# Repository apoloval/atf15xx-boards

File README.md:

# ATF15xx Boards

This repository contains PCB designs for programming and prototyping boards for Atmel ATF15xx CPLDs family.

## Contents

- [atf15xxprog-plcc44](./atf15xxprog-plcc44): A broadboard adapter with JTAG connector to program ATF1502 and ATF1504 CPLDs with PLCC44 packaging.

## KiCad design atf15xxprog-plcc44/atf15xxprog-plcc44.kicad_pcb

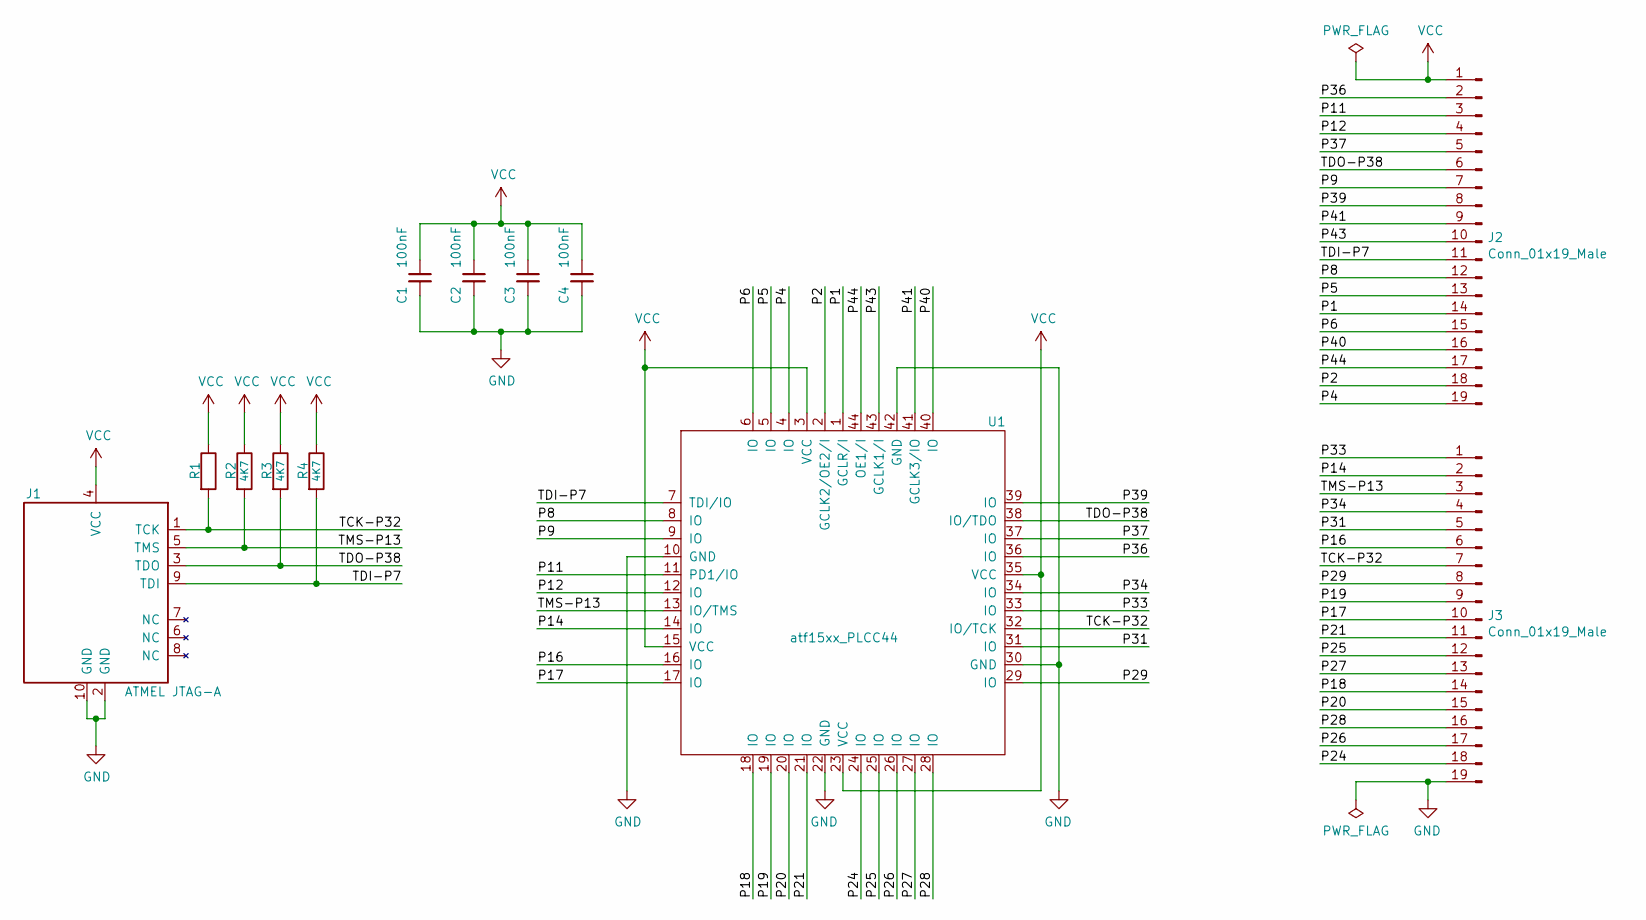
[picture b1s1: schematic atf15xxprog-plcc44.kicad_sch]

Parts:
C1, C2, C3, C4: 100nF; C_1206_3216Metric
J1: ATMEL JTAG-A; IDC-Header_2x05_P2.54mm_Vertical
J2, J3: Conn_01x19_Male; PinHeader_1x19_P2.54mm_Vertical
R1: (no value)
R2, R3, R4: 4K7
U1: atf15xx_PLCC44; PLCC-44_THT-Socket

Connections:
/P1: J2.14, U1.1 (GCLR/I)
/P2: J2.18, U1.2 (GCLK2/OE2/I)
/P4: J2.19, U1.4 (IO)
/P5: J2.13, U1.5 (IO)
/P6: J2.15, U1.6 (IO)
/P8: J2.12, U1.8 (IO)
/P9: J2.7, U1.9 (IO)
/P11: J2.3, U1.11 (PD1/IO)
/P12: J2.4, U1.12 (IO)
/P14: J3.2, U1.14 (IO)
/P16: J3.6, U1.16 (IO)
/P17: J3.10, U1.17 (IO)
/P18: J3.14, U1.18 (IO)
/P19: J3.9, U1.19 (IO)
/P20: J3.15, U1.20 (IO)
/P21: J3.11, U1.21 (IO)
/P24: J3.18, U1.24 (IO)
/P25: J3.12, U1.25 (IO)
/P26: J3.17, U1.26 (IO)
/P27: J3.13, U1.27 (IO)
/P28: J3.16, U1.28 (IO)
/P29: J3.8, U1.29 (IO)
/P31: J3.5, U1.31 (IO)
/P33: J3.1, U1.33 (IO)
/P34: J3.4, U1.34 (IO)
/P36: J2.2, U1.36 (IO)
/P37: J2.5, U1.37 (IO)
/P39: J2.8, U1.39 (IO)
/P40: J2.16, U1.40 (IO)
/P41: J2.9, U1.41 (GCLK3/IO)
/P43: J2.10, U1.43 (GCLK1/I)
/P44: J2.17, U1.44 (OE1/I)
/TCK-P32: J1.1 (TCK), J3.7, R1.2, U1.32 (IO/TCK)
/TDI-P7: J1.9 (TDI), J2.11, R4.2, U1.7 (TDI/IO)
/TDO-P38: J1.3 (TDO), J2.6, R3.2, U1.38 (IO/TDO)
/TMS-P13: J1.5 (TMS), J3.3, R2.2, U1.13 (IO/TMS)
GND: C1.2, C2.2, C3.2, C4.2, J1.2 (GND), J1.10 (GND), J3.19, U1.10 (GND), U1.22 (GND), U1.30 (GND), U1.42 (GND)
VCC: C1.1, C2.1, C3.1, C4.1, J1.4 (VCC), J2.1, R1.1, R2.1, R3.1, R4.1, U1.3 (VCC), U1.15 (VCC), U1.23 (VCC), U1.35 (VCC)

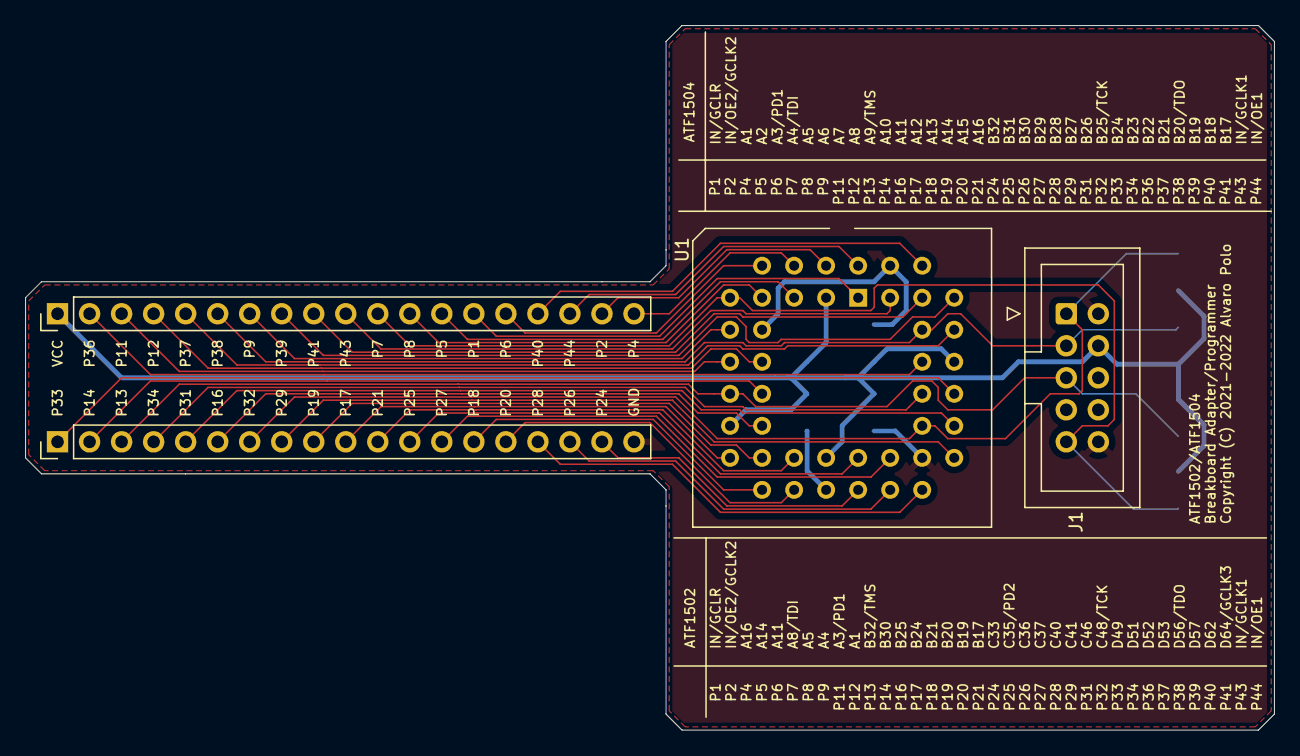
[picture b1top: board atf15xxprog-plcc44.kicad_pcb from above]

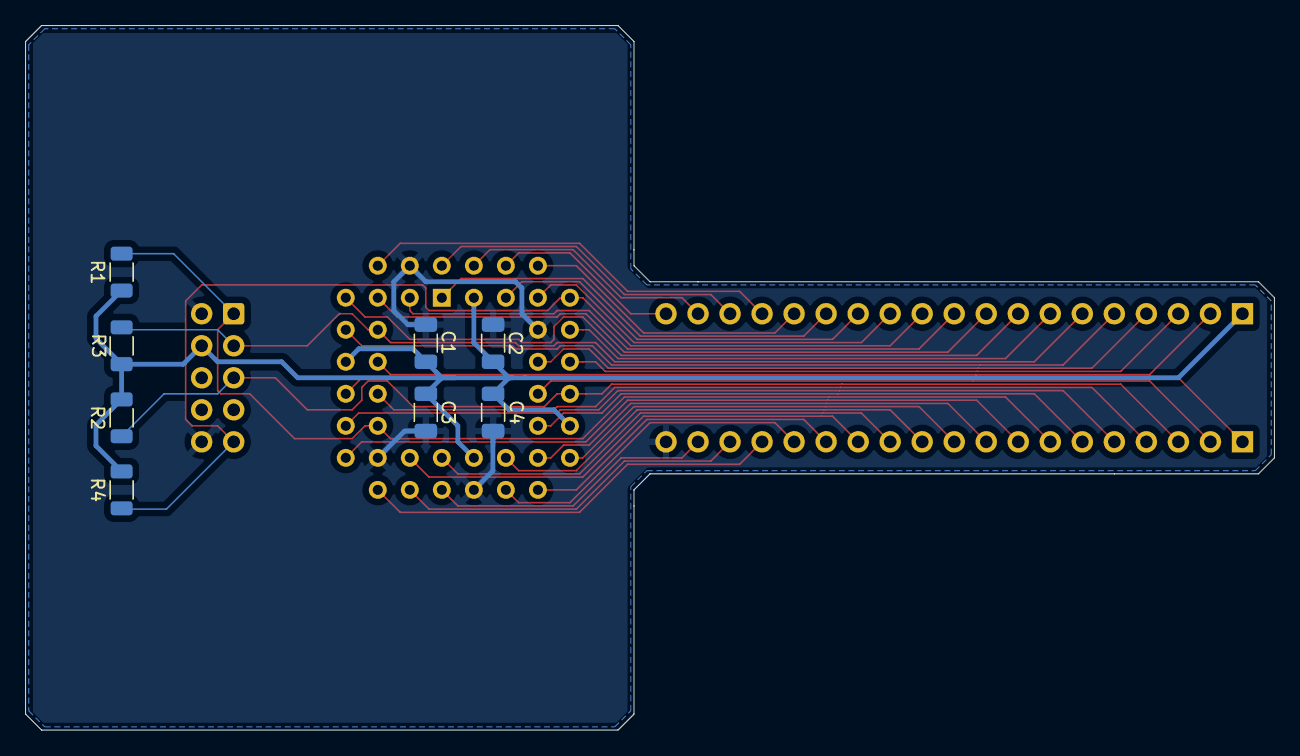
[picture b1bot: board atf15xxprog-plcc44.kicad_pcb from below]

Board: 2 copper layers, 99.1 x 55.9 mm, 12 parts (8 on the bottom side), 38 nets.

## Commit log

2022-08-11 Make it so
2022-08-11 atf15xxprog-plcc44: new board
2022-08-11 atf15xxprog-plcc44: migrate sym lib to v6 format
2022-08-11 atf15xxprog-plcc44: use a custom JTAG-A symbol
2022-08-11 atf15xxprog-plcc44: fix tiny fonts in texts
2022-08-12 atf15xxprog-plcc44: add pull-up resistors for JTAG

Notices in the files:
atf15xxprog-plcc44/atf15xxprog-plcc44.kicad_pcb:
Copyright (C) 2021-2022 Alvaro Polo
